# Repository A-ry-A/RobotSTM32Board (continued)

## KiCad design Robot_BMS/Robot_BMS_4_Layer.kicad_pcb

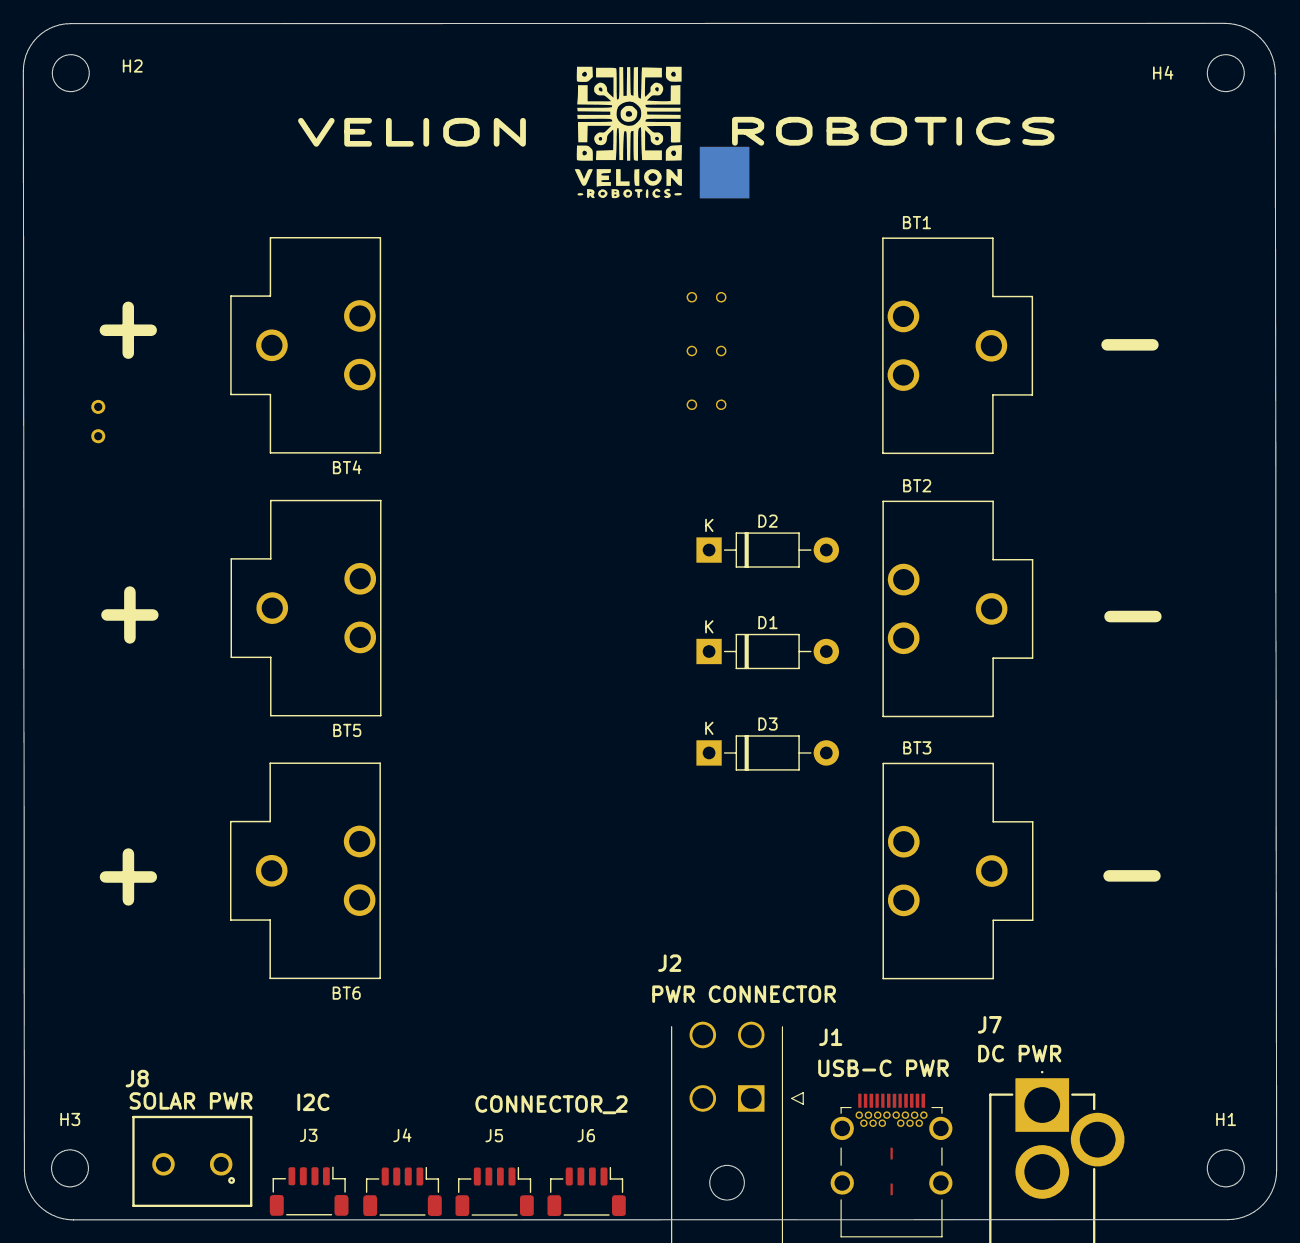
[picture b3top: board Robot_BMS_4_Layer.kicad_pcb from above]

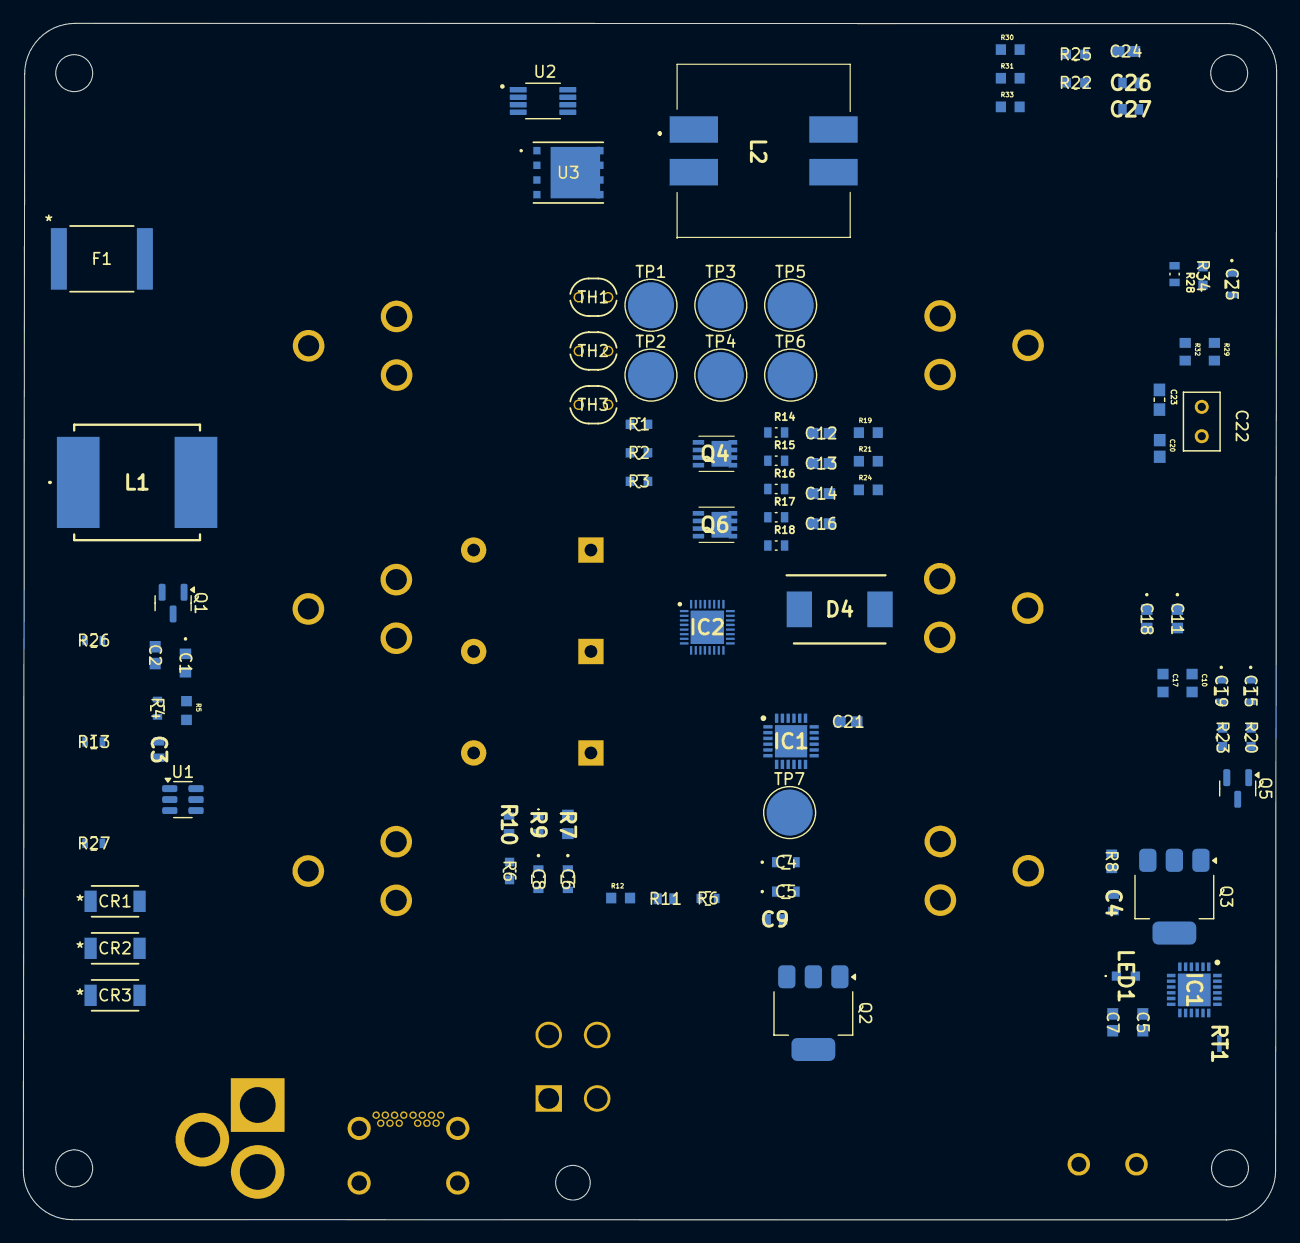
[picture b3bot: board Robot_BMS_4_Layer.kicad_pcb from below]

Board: 4 copper layers, 108.6 x 103.7 mm, 116 parts (95 on the bottom side), 74 nets, no tracks yet.

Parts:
BT1, BT2, BT3, BT4, BT5, BT6: BK-18650-CLIP; BAT_BK-18650-CLIP
C1, C11, C18: 2.2u; CAP_GRM188R61H225KE11__MUR
C2, C5, C7, C12, C13, C14, C16, C21: 0.1u; CAPC17595_87N_KEM
C3, C4#2, C9, C26, C27: 10u; CAPC1608X90N
C4, C5#2, C6, C8, C19, C25: 1u; CAP_1608_TDK
C10, C17: 100p; CAPC1608X97N
C15: 0.47u; CAP_1608_TDK
C20: 4.7u; CAPC1608X120N
C22: 1n; CAPRR254W50L508T317H508
C23: 180n; CAPC1608X90
C24: 820p; CAPC17795_95N_KEM
CR1, CR2, CR3: CMS05TE12L_Q_M; M-FLAT_TOS
D1, D2, D3: 1N4750A; D_DO-41_SOD81_P10.16mm_Horizontal
D4: B370-13-F; DIOM7959X250N
F1: MF-LSMF500/16X-2; FUSE_MF-LSMF185&slash_33X_BRN
H1, H2, H3, H4: MountingHole; MountingHole_3.2mm_M3
IC1: AP33772DKZ-13; QFN50P400X400X80-25N-D
IC1#2: STUSB4710AQTR; QFN50P400X400X100-25N-D
IC2: BQ76922RSNR; QFN40P400X400X80-33N-D
J1: 632723300011
J2: 39-30-0040; 39-30-Y040
J3, J4, J5, J6: Qwiik1; JST_SH_BM04B-SRSS-TB_1x04-1MP_P1.00mm_Vertical
J7: 694108301002
J8: 691137710002
L1: ETQ-P5M220YSC; ETQP5M220YSC
L2: MSD1583-223MEB; MSD1583223MEB
LED1: SML-D12V8WT86; SMLD12V8WT86
Q1, Q5: 2N7002; SOT-23
Q2, Q3: NDT3055L; SOT-223-3_TabPin2
Q4, Q6: SIS413DN-T1-GE3; SIS862DNT1GE3
R1, R2, R3: 3k24; RC0603N_YAG
R4, R6#2, R13, R26, R27: 100k; RES_R0603_ROM
R5: 4.81k; RESC1608X55N
R6, R22, R23, R25, R34: 10k; RC0603N_YAG
R7: 10 milli_ohm; RESC1608X60N
R8, R11: 1k; RES_V0603_VIS
R9, R10: 5k1; ERA3AEB101V
R12, R19, R21, R24, R31: 100; RESC1608X55N
R14, R15, R16, R17, R18, R28: 20; RES_ERJPA3F20R0V
R20: 1 mOhm; RC0603N_YAG
R29: 604; RESC1508X50N
R30: 40k2; RESC1608X55N
R32: 13 milli_Ohm; RESC1508X50N
R33: 110k; RESC1608X55N
RT1: 10k; THRMC0603X33N
TH1, TH2, TH3: 10K; THERMISTORS_100E3103HB0_VIS
TP1, TP2: NTC1; TestPoint_Pad_D4.0mm
TP3, TP4: NTC2; TestPoint_Pad_D4.0mm
TP5, TP6: NTC3; TestPoint_Pad_D4.0mm
TP7: VBUS_Test; TestPoint_Pad_D4.0mm
U1: TPS54308DDCR; SOT-23-6
U2: LM3488MM; SOP65P490X110-8N
U3: CSD18563Q5A; DQJ8

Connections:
3V3: J3.3, R1.1, R2.1, R3.1, R22.2
/Battery Management/ALERT: IC2.16 (ALERT), J4.4, R22.1
/Battery Management/LD: IC2.28 (LD), R25.1
/Battery Management/MCU_CHRG_CTRL: IC2.19 (CFETOFF), J5.1
/Battery Management/MCU_DISCHRG_CTRL: IC2.20 (DFETOFF), J5.2
/Battery Management/SCL: IC1.5 (SCL), IC1#2.7 (SCL), IC2.17 (SCL), J3.1
/Battery Management/SDA: IC1.4 (SDA), IC1#2.8 (SDA), IC2.18 (SDA), J3.2
/Battery Management/TO_LOAD: F1.2, J2.3, J2.4
/Charging Circuit/CHARGE_IN: C1.2, CR1.2, CR2.2, CR3.2, U1.3 (VIN)
/Charging Circuit/DC_BARREL_JACK: CR3.1, D2.1 (K), J7.1
/Charging Circuit/MCU_CHARGE_EN: J5.4, Q1.1 (G)
/Charging Circuit/SOLAR_15V_OUT: C26.2, C27.2, CR2.1, D4.1 (K), R33.2
/Charging Circuit/USB_C: C8.1, CR1.1, IC1.22 (VBUS), Q3.3 (S)
/Solar Power/DR_Source: R31.1, R32.2, U3.1 (S), U3.2 (S), U3.3 (S)
/Solar Power/Isense: C24.1, R31.2, U2.1 (ISEN)
/Solar Power/SOLAR_VIN: C20.2, D3.1 (K), J8.2, L2.3, R28.2
/Thermistors/ADC1_MCU: J4.1, R1.2, TP1.1
/Thermistors/ADC2_MCU: J4.2, R2.2, TP3.1
/Thermistors/ADC3_MCU: J4.3, R3.2, TP5.1
/To MCU OR System/USB_C_Interrupt: IC1.9 (GPIO3), J6.1
/USB-C/CC1: IC1.17 (CC1), IC1#2.2 (CC1), J1.A5 (CC1), R10.1
/USB-C/CC2: IC1.16 (CC2), IC1#2.4 (CC2), J1.B5 (CC2), R9.1
/USB-C/D+: J1.A6 (DP1), J1.B6 (DP2), R12.2
/USB-C/D-: J1.A7 (DN1), J1.B7 (DN2), R12.1
/USB-C/FAULT: IC1.6 (GPIO4), R6.1
/USB-C/VCC: IC1.24 (VCC), Q2.2 (D), R7.2
BATT+: BT4.1_1, BT4.1_2, BT4.1_3, C3.2, C10.1, C11.2, C15.1, IC2.1 (BAT), L1.2, Q4.5 (D_1), Q4.6 (D_2), Q4.7 (D_3), Q4.8 (D_4), R4.2, R17.1, R24.2
GND: BT3.1_1, BT3.1_2, BT3.1_3, C1.1, C3.1, C4.2, C4#2.2, C5.2, C5#2.2, C6.2, C7.2, C8.2, C9.1, C10.2, C11.1, C12.2, C18.1, C19.2, C20.1, C21.2, C22.1, C23.2, C24.2, C26.1, C27.1, IC1.3 (GND_1), IC1.25 (GND_2), IC1#2.10 (GND), IC1#2.14 (SEL_PDO4), IC1#2.25 (EP), IC2.10 (VSS), IC2.33 (EP), J1.1 (GND_1), J1.2 (GND_2), J1.A1 (GND_3), J1.A12 (GND_4), J1.B1 (GND_5), J1.B12 (GND_6), J2.1, J2.2, J3.4, J5.3, J7.2, J7.3, J8.1, L2.4, LED1.1 (K), Q1.2 (S), R5.2, R6#2.1, R9.2, R10.2, R11.2, R13.1, R18.1, R19.1, R20.1, R20.2, R21.1, R26.1, R27.1, R30.1, R32.1, R34.1, RT1.2, TP2.1, TP4.1, TP6.1, U1.1 (GND), U2.4 (AGND), U2.5 (PGND)
unnamed: BT1.1_1, BT1.1_2, BT1.1_3, BT5.1_1, BT5.1_2, BT5.1_3, R15.1, R16.1
unnamed: BT2.1_1, BT2.1_2, BT2.1_3, BT6.1_1, BT6.1_2, BT6.1_3, R14.1
unnamed: C23.1, R29.1
unnamed: C25.1, L2.1, U3.5 (D), U3.6 (D), U3.7 (D), U3.8 (D)
unnamed: D1.2 (A), R13.2
unnamed: D2.2 (A), R26.2
unnamed: D3.2 (A), R27.2
unnamed: C25.2, D4.2 (A), L2.2
unnamed: IC1#2.13 (ADDR0), R6#2.2
unnamed: C7.1, IC1.15 (IFB)
unnamed: IC1.13 (OTP), RT1.1
unnamed: IC1.23 (PWR_EN), R8.2
unnamed: C5.1, IC1.12 (V3VD)
unnamed: C6.1, IC1.20 (V5V)
unnamed: C5#2.1, IC1#2.21 (VREG_1V2)
unnamed: C4.1, IC1#2.23 (VREG_2V7)
unnamed: IC2.24 (BREG), Q5.1 (G)
unnamed: IC2.31 (CHG), Q4.4 (G)
unnamed: C15.2, IC2.32 (CP1)
unnamed: IC2.30 (DSG), Q6.4 (G)
unnamed: IC2.29 (PACK), R23.1
unnamed: C19.1, IC2.22 (REG1)
unnamed: C18.2, IC2.15 (REG18)
unnamed: IC2.23 (REGIN), Q5.2 (S)
unnamed: C16.2, C17.2, IC2.12 (SRN), R21.2
unnamed: C16.1, C17.1, IC2.11 (SRP), R19.2
unnamed: C12.1, IC2.9 (VC0), R18.2
unnamed: C14.2, IC2.8 (VC1), R14.2
unnamed: C13.2, C14.1, IC2.3 (VC4A), IC2.4 (VC4B), IC2.5 (VC3A), IC2.6 (VC3B), IC2.7 (VC2), R15.2, R16.2
unnamed: C13.1, IC2.2 (VC5), R17.2
unnamed: LED1.2 (A), R6.2
unnamed: Q1.3 (D), U1.5 (EN)
unnamed: Q2.1 (G), Q3.1 (G), R8.1
unnamed: Q2.3 (S), Q3.2 (D)
unnamed: Q4.1 (S_1), Q4.2 (S_2), Q4.3 (S_3), Q6.5 (D_1), Q6.6 (D_2), Q6.7 (D_3), Q6.8 (D_4)
unnamed: Q5.3 (D), R24.1
unnamed: F1.1, Q6.1 (S_1), Q6.2 (S_2), Q6.3 (S_3), R23.2, R25.2
unnamed: C2.1, U1.6 (BOOT)
unnamed: R4.1, R5.1, U1.4 (FB)
unnamed: C2.2, L1.1, U1.2 (SW)
unnamed: C22.2, R29.2, U2.2 (COMP)
unnamed: U2.6 (DR), U3.4 (G)
unnamed: R30.2, U2.7 (FA/SYNC/SD)
unnamed: R33.1, R34.2, U2.3 (FB)
unnamed: C21.1, R28.1, U2.8 (VIN)
VBUS: C4#2.1, C9.2, D1.1 (K), IC1.1 (ISENP), IC1#2.18 (VBUS_SENSE), IC1#2.24 (VDD), J1.A4 (VBUS_1), J1.A9 (VBUS_2), J1.B4 (VBUS_3), J1.B9 (VBUS_4), R7.1, R11.1, TP7.1

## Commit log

2025-03-03 added motor stuff to schematic and IC
2025-03-10 did motor driver and sttuff
2025-03-10 Robot_BMS folder containg BMS_Schematic added
2025-03-10 changed board to the one peter wilson gave us
2025-03-10 NTC's implemented
2025-03-10 Battery Protection IC implemented, N Channel Fet selected
2025-03-11 comments on Bat Protection IC added
2025-03-11 Li+ Ion implemented into schematic for one of the cells
2025-03-11 Removed USB-C PD chip in favor of using resistors to neogitate 5V 3A (15W) charging
2025-03-12 working on thee fuel gauge
2025-03-12 implementing hierarchical schematics
2025-03-12 cleaning up hierarchical schematics
2025-03-13 added the buck converters
2025-03-13 added buck converter 6v to schematic
2025-03-15 DC power supply added via dc Barrel jack
2025-03-17 implementing sepic converter for Solar power input
2025-03-17 USB-c PD to 15V
2025-03-17 solar charger set to 15V
2025-03-18 pcb layout for the buck converters started
2025-03-18 ex charging circuit last appearence
2025-03-18 battery management ic is being added
2025-03-18 System drawing down on top schematic, will start inputting footprints
2025-03-19 adding footprints and actual passive components
2025-03-19 adding footprints and actual passive components pt.2
2025-03-19 still adding in symbols & footprints for passives
2025-03-19 all symbols footprints & models added
2025-03-20 BOM done, with total price £40
2025-03-24 switching usb c pd chip to ap33772 due to better support online
2025-03-24 mid way implementing new usb-pd chip
2025-03-24 placed connectors for BMS PCB
2025-03-24 Battery holders placed for 18650 fit
2025-03-27 adding qwik connectors replacing old jst ph 6 pin ones
2025-03-27 qwikk connector 3d model and footprint in RobotBMS
2025-03-27 creation of seperate 4 layer pcb for individual technical report
2025-04-01 corrected buck converters
2025-04-01 PCB layout up to charging circuit
2025-04-03 halfway throgh battery management pcb layout
2025-04-11 pcb routed
2025-04-11 added dc in
2025-04-11 first pcb layout done, beginning of DRC checks
2025-04-13 correcting DRC's
2025-04-15 resize board for chanin m2.5 holes
2025-04-15 drc's resolved
2025-04-15 drc's solved
2025-04-17 Added battery connectors
2025-04-17 added fuse
2025-04-18 manufacture ready
2025-05-19 commit of the finished thing before i tidy it up for the report
